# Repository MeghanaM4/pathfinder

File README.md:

# pathfinder
make a custom PCB controller board and efidget, get the money and parts to build it. Check out [pathfinder.hackclub.com](https://pathfinder.hackclub.com) to see the guide and the [gallery](https://pathfinder.hackclub.com/gallery) to see the project submitted from all over the world!

### My Pathfinder

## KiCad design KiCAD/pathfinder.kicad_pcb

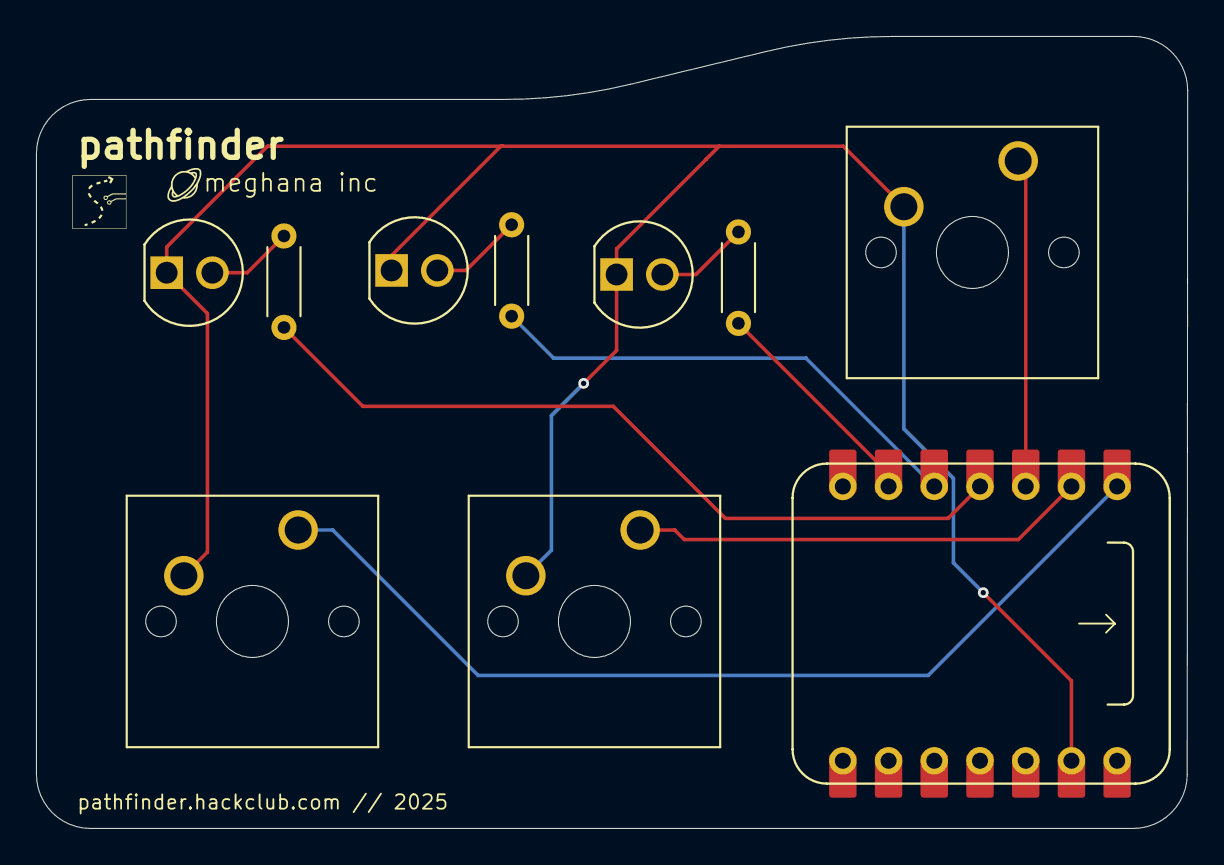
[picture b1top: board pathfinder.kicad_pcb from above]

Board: 2 copper layers, 64.0 x 44.0 mm, 10 parts (0 on the bottom side), 10 nets.

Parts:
LED1, LED2, LED3: L08R5000Q1; LEDRD254W57D500H1070
R1, R2, R3: R; R_Axial_DIN0204_L3.6mm_D1.6mm_P5.08mm_Horizontal
SW1, SW2, SW3: SW_Push; SW_Cherry_MX_1.00u_PCB
U1: XIAO-RP2040-DIP

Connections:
GND: LED1.C, LED2.C, LED3.C, SW1.2, SW2.2, SW3.2, U1.13 (GND)
LED1: R1.2, U1.4 (GPIO29/ADC3/A3)
LED2: R2.2, U1.5 (GPIO6/SDA)
LED3: R3.2, U1.6 (GPIO7/SCL)
unnamed: LED1.A, R1.1
unnamed: LED2.A, R2.1
unnamed: LED3.A, R3.1
button1: SW1.1, U1.1 (GPIO26/ADC0/A0)
button2: SW2.1, U1.2 (GPIO27/ADC1/A1)
button3: SW3.1, U1.3 (GPIO28/ADC2/A2)

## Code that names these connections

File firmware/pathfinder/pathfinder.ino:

int BUT1 = D0;  //assigning pin numbers for all the components
int BUT2 = D1;  //these numbers probably won't work for you,
int BUT3 = D2;  //check the XIAO RP2040's pinout and your PCB editor to find yours

int LED1 = D3;
int LED2 = D4;
int LED3 = D5;

void setup() {
  pinMode(BUT1, INPUT_PULLUP);  //you have to do this so Arduino know to set internal pull-up resistors correctly
  pinMode(BUT2, INPUT_PULLUP);  //buttons are inputs (user does an action)
  pinMode(BUT3, INPUT_PULLUP);

  pinMode(LED1, INPUT_PULLUP);  //LEDs are outputs (result of action)
  pinMode(LED2, INPUT_PULLUP);
  pinMode(LED3, INPUT_PULLUP);

  long startTime = millis();  //log official start time (optional)
}

void loop() {
  long but1time;
  long but2time;
  long but3time = 0;

  if (digitalRead(BUT1) == HIGH) {  //this code block says "if button 1 is pressed then turn on LED 1"
    but1time = millis();            //logs time button 1 was pressed
    digitalWrite(LED1, HIGH);       //buttons and LEDs are digital components, so that's why it's digitalRead and digitalWrite
  } else {
    digitalWrite(LED1, LOW);
  }

  if (digitalRead(BUT2) == HIGH) {  //logs time that button 2 was pressed
    but2time = millis();
  }

  if (abs(but2time - but1time) <= 2000) {  //if button 1 and button 2 were pressed within 2 seconds of each other, then LED 2 lights up
    digitalWrite(LED2, HIGH);
  } else {
    digitalWrite(LED2, LOW);  //we have to do this or else LED 2 will always stay on
  }

  if (digitalRead(BUT3) == HIGH) {  //this keeps track of how long button 3 has been pressed
    but3time++;
  } else {
    but3time = 0;  //if not pressed then set time back to 0
  }

  if (but3time >= 800) {  //if it's pressed for more than 800 loops then turn LED3 on
    digitalWrite(LED3, HIGH);
  } else {
    digitalWrite(LED3, LOW);
  }
  
}

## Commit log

2025-06-24 initial stuff
2025-06-24 treasure map
2025-06-25 schematic tutorial
2025-06-27 pcb making + firmware
2025-06-27 firmware guide
2025-06-27 Create CNAME
2025-06-27 code formatting
2025-06-27 fillout
2025-06-27 3d models
2025-06-27 broken button
2025-06-27 favicon
2025-06-28 render
2025-06-28 scroll text
2025-06-28 date
2025-06-28 responsiveness? I hardly know her
2025-07-02 fix link
2025-07-02 Ordering
2025-07-03 prod folder + how to buy
2025-07-03 organization
2025-07-03 fixing dumb mistake
2025-07-03 render file path
2025-07-04 led link
2025-07-05 highlight + extension
2025-07-07 whoopsies
2025-07-07 my bad guys
2025-07-07 project gallery (locked in)
2025-07-07 favicon and title
2025-07-08 peegee on main
2025-07-08 hopefully this works
2025-07-19 kicad wakatime setup
2025-07-21 caching :bangbang:
2025-07-22 wrench
2025-07-22 better firmware (sorry guys)
2025-07-22 Don't remember
2025-07-22 end date
2025-07-23 help button
2025-07-23 help btn format
2025-07-24 Forgot
2025-08-17 fix gallery git repo link
2025-08-19 fix gallery
2025-09-08 fixing CAD model links + caching
2025-10-15 Pathfinder: Halloween Edition
2025-12-04 turn off caching
2025-12-05 fix airbridge url
2025-12-08 change pathfinder background (kicad also updated PCB)
2025-12-09 fix pfc link
2026-02-05 no more cdn
